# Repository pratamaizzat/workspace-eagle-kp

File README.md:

Merupakan repository kumpulan file eagle untuk project kp

1. Powes Supply Unit
2. Reangkaian Receiver VLC
3. Rangkaian TIA VLC

Pending : Menambahkan komponen filter HPF pada Rangkaian Sheet 2

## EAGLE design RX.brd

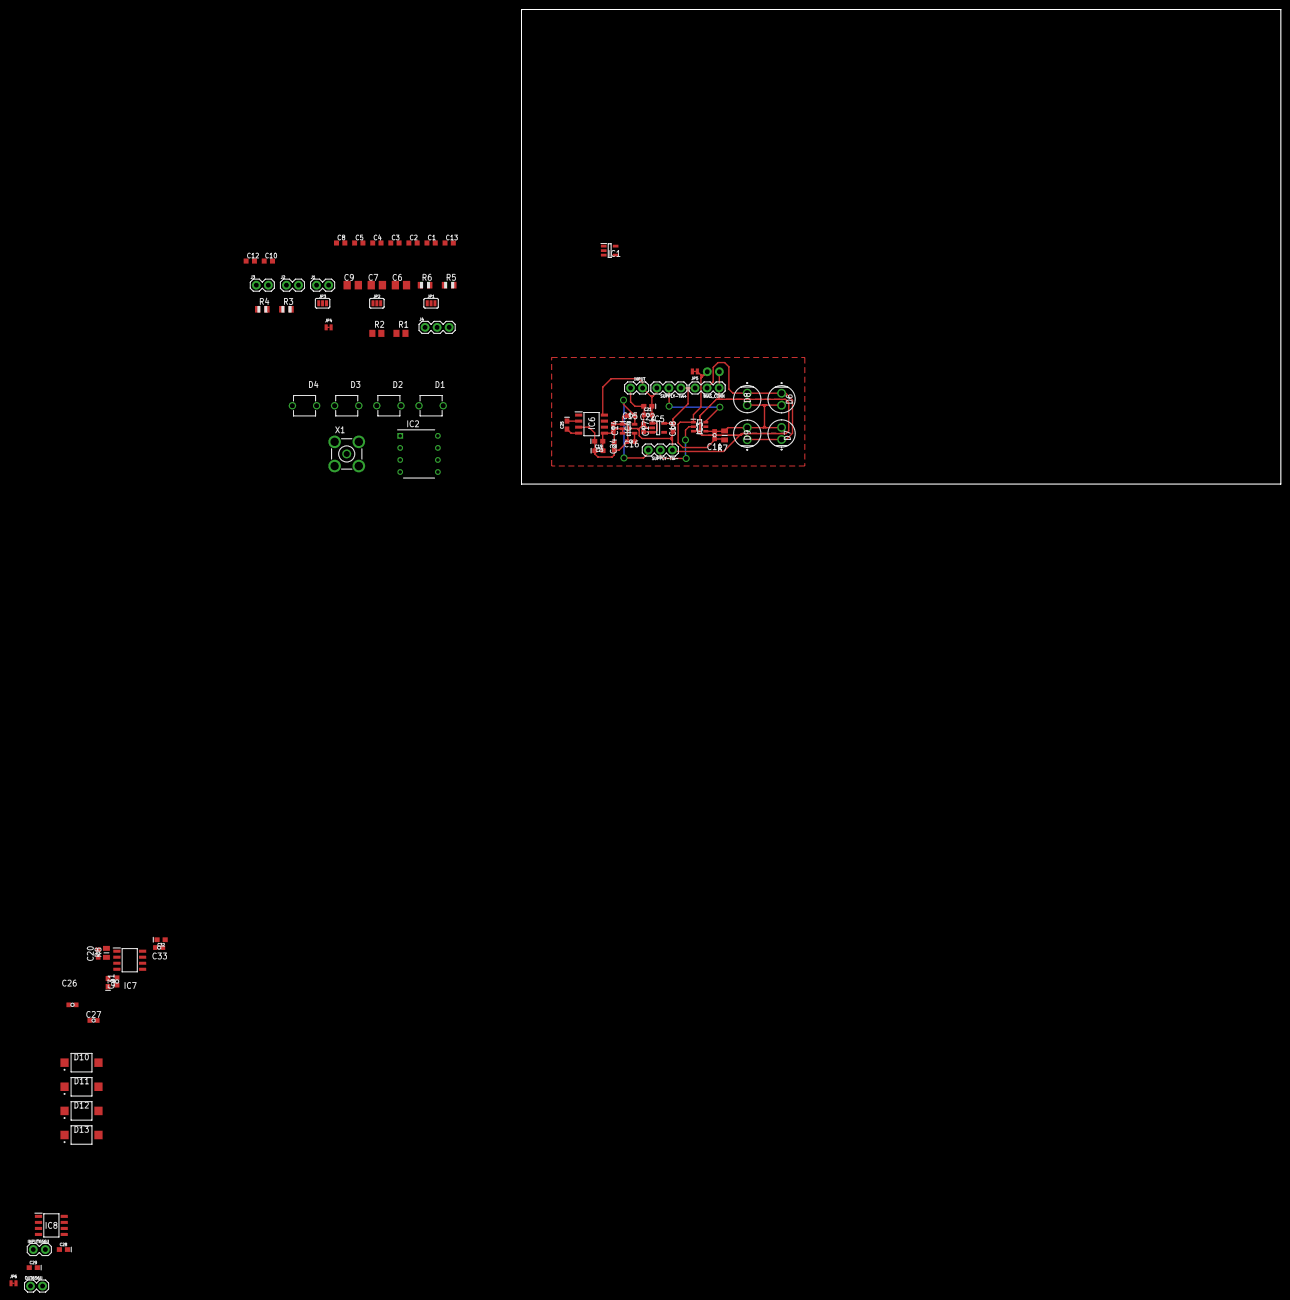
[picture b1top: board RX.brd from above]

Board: 2 copper layers, 160.0 x 100.0 mm, 79 parts (1 on the bottom side), 35 nets.

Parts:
BIAS_CONN: 455-1750-1-ND; 1X03
C1, C2, C3, C4, C5, C8, C10, C12, C13: C0603K
C6, C7, C9: R/2012-12R
C11, C14, C15, C16, C17, C18, C20, C22, C24, C26, C27, C31, C33: 06033C104KAZ2A; CAPC1608X90N
C19, C21, C23, C25, C28, C29, C30, C32: 10uF; 0603-POLAR
D1, D2, D3, D4: BPW34
D6, D7, D8, D9: BPV10NF
D10, D11, D12, D13: VBPW34SR
IC1: OPA354AIDBVR; SOT95P280X145-5N@1
IC2: LM7171BIN_NOPB; DIP794W53P254L959H508Q8N
IC3: LTC6268IS6-10#TRMPBF; SOT95P280X90-6N
IC4: TPS72325DBVTG4; SOT95P280X145-5N
IC5: TLV75525PDBVR; SOT95P280X145-5N
IC6, IC8: TC7662BEOA; SOIC127P600X175-8N
IC7: OPA656U; SOIC127P600X175-8N@1
INPUT, INPUT656U: 1X02
J1, J2, J3: 1X02
J4: 455-1750-1-ND; 1X03
JP1, JP2, JP3: JUMPER-SMT_3_NO_SILK; SMT-JUMPER_3_NO_SILK
JP4, JP5, JP6: JUMPER-SMT_2_NC_TRACE_NO-SILK; SMT-JUMPER_2_NC_TRACE_NO-SILK
OUT656U: 1X02
OUTPUT_LTC: 1X02
R1, R2, R3, R4, R5, R6: R0805
R7, R8: RG2012P-275-B-T5; RESC2012X50N
SUPPLY-TIA+: 455-1750-1-ND; 1X03
SUPPLY-TIA-: 455-1750-1-ND; 1X03
X1: BU-SMA-V

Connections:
5V: C3.2, C4.2, C6.+, C7.+, IC1.5, IC2.7, J4.2
+2.5V: BIAS_CONN.1, C18.2, IC5.5, SUPPLY-TIA+.3
+5V: C17.2, C21.+, C22.2, IC5.1, IC5.3, IC6.8, INPUT.1, SUPPLY-TIA+.1
+V656U: C32.+, C33.2, IC7.7, IC8.8, INPUT656U.1
-2.5V: C15.2, IC4.5, SUPPLY-TIA-.1
-5V: C8.1, C9.-, IC2.4, J4.3
-5V_LTC: C14.2, C19.-, C24.2, IC4.2, IC4.3
-IN: C1.1, C2.2, D1.1, D2.1, D3.1, D4.1, IC1.4, R1.1
-V656U: C29.-, C30.-, C31.2, IC7.4, IC8.5
AMP_IN: JP4.1, R6.1
BIAS_PD: D1.2, D2.2, D3.2, D4.2, JP1.2
GND: C2.1, C3.1, C4.1, C5.1, C6.-, C7.-, C8.2, C9.+, C12.1, J1.2, J2.1, J3.2, J4.1, JP1.3, JP2.3, JP3.3, R2.1, R4.1, X1.2, X1.3, X1.4, X1.5
GND2: BIAS_CONN.3, C14.1, C15.1, C16.1, C17.1, C18.1, C19.+, C21.-, C22.1, C23.+, C24.1, IC3.3, IC4.1, IC5.2, IC6.3, INPUT.2, OUTPUT_LTC.1, SUPPLY-TIA-.3
GND3: C26.1, C27.1, C29.+, C30.+, C31.1, C32.-, C33.1, IC7.3, IC8.3, INPUT656U.2, OUT656U.2
unnamed: IC1.3, JP3.2
unnamed: C20.1, C26.2, C27.2, D10.2, D11.2, D12.2, D13.2, IC7.2, R8.1
unnamed: C1.2, C5.2, IC1.1, J1.1, JP4.2, R1.2, R2.2
unnamed: J3.1, JP1.1
unnamed: IC1.2, JP2.2
unnamed: C10.1, IC2.2, R3.1, R4.2
unnamed: C12.2, IC2.3, R5.2
unnamed: C13.2, R5.1, R6.2
unnamed: C16.2, IC4.4
unnamed: C11.1, IC3.1, JP5.1, OUTPUT_LTC.2, R7.1
unnamed: C25.+, IC6.2
unnamed: C25.-, IC6.4
unnamed: C20.2, IC7.6, JP6.1, OUT656U.1, R8.2
unnamed: C11.2, D6.2, D7.2, D8.2, D9.2, IC3.4, R7.2
unnamed: C28.+, IC8.2
unnamed: C28.-, IC8.4
OUT_AMP: C10.2, C13.1, IC2.6, J2.2, R3.2, X1.1
V+: IC3.6, SUPPLY-TIA+.2
V-: IC3.2, SUPPLY-TIA-.2
V_BIAS: BIAS_CONN.2, D6.1, D7.1, D8.1, D9.1
V_BIAS656U: D10.1, D11.1, D12.1, D13.1

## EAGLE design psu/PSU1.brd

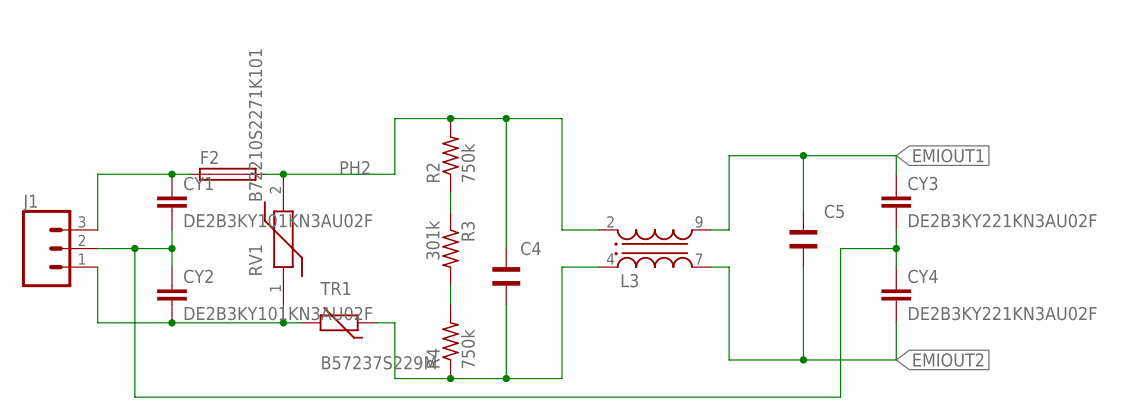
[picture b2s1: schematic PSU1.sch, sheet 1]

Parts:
C4, C5: WCAP-FTXX_890334025039CS; WCAP-FTXX_15X18X14X8
CY1, CY2: DE2B3KY101KN3AU02F; YC7B5
CY3, CY4: DE2B3KY221KN3AU02F; YC7B5
F2: GSH15
J1: CONN_03-SCREW-5MM; SCREWTERMINAL-5MM-3
L3: WE-CMB_L_744824310; WE-CMB_L
R2, R4: 750k; R1206
R3: 301k; R1206
RV1: B72210S2271K101
TR1: B57237S229M; R-7,5

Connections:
EMIOUT1: C5.2, CY3.1, L3.9 (3); also elsewhere on the board
EMIOUT2: C5.1, CY4.2, L3.7 (2); also elsewhere on the board
unnamed: R2.1, R3.1
unnamed: R3.2, R4.2
unnamed: CY1.1, F2.1, J1.3
unnamed: CY2.2, J1.1, RV1.1, TR1.2
unnamed: C4.2, L3.4 (1), R4.1, TR1.1
unnamed: CY1.2, CY2.1, CY3.2, CY4.1, J1.2
PH2: C4.1, F2.2, L3.2 (4), R2.2, RV1.2

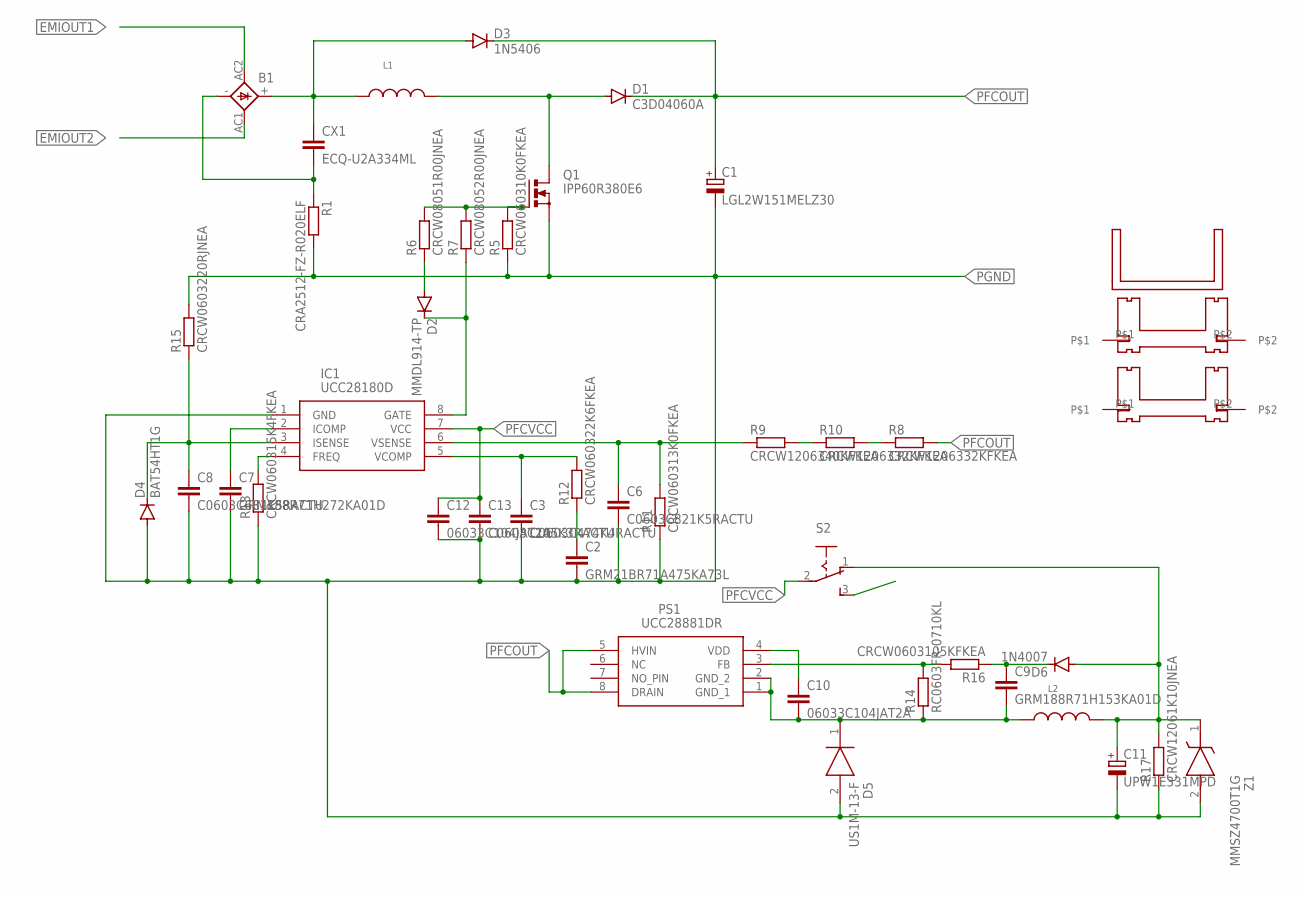
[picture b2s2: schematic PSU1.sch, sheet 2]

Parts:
B1: GBU4S
C1: LGL2W151MELZ30; EB22,5D
C2: GRM21BR71A475KA73L; C0805
C3: C0603C474K4RACTU; C0603
C6: C0603C821K5RACTU; C0603
C7: GRM188R71H272KA01D; C0603
C8: C0603C681K5RACTU; C0603
C9: GRM188R71H153KA01D; C0603
C10, C12: 06033C104JAT2A; C0603
C11: UPW1E331MPD; E5-10,5
C13: C0603C105K3RACTU; C0603
CX1: ECQ-U2A334ML; XC15B10
D1: C3D04060A; TO220ACS
D2: MMDL914-TP; SOD323-R
D3: 1N5406; DO201-15
D4: BAT54HT1G; SOD323-R
D5: US1M-13-F; SODFL5226X240N
D6: 1N4007; DO41-7.6
IC1: UCC28180D; SOIC127P600X175-8N
L1: WE-HCF_ROUND_74437529203471; WE-HCF_ROUND
L2: WE-TIS_1111_7447471102; WE-TIS_1111
PS1: UCC28881DR; SOIC127P600X175-8N
Q1: IPP60R380E6; TO220BV
R1: CRA2512-FZ-R020ELF; R2512W
R5: CRCW060310K0FKEA; R0603
R6: CRCW08051R00JNEA; R0805
R7: CRCW08052R00JNEA; R0805
R8, R10: CRCW1206332KFKEA; R1206
R9: CRCW1206340KFKEA; R1206
R11: CRCW060313K0FKEA; R0603
R12: CRCW060322K6FKEA; R0603
R13: CRCW060315K4FKEA; R0603
R14: RC0603FR-0710KL; R0805
R15: CRCW0603220RJNEA; R0603
R16: CRCW0603105KFKEA; R0805
R17: CRCW12061K10JNEA; R1206
S2: 255SB
U$1, U$3: HEAT001; HEAT01
U$2: HEAT002; HEAT02
Z1: MMSZ4700T1G; SOD3716X135N

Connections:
DMOS1: D1.A, L1.2, Q1.D
EMIOUT1: B1.AC2 (AC1); also elsewhere on the board
EMIOUT2: B1.AC1 (AC2); also elsewhere on the board
unnamed: Q1.G, R5.2, R6.2, R7.2
unnamed: B1.-, CX1.2, R1.1
unnamed: B1.+, CX1.1, D3.A, L1.1
unnamed: D2.A, R6.1
unnamed: D2.C, IC1.8 (GATE), R7.1
unnamed: R8.1, R10.2
unnamed: R9.2, R10.1
unnamed: C6.1, IC1.6 (VSENSE), R9.1, R11.2
unnamed: C3.1, IC1.5 (VCOMP), R12.2
unnamed: IC1.4 (FREQ), R13.2
unnamed: C8.1, D4.C, IC1.3 (ISENSE), R15.1
unnamed: C7.1, IC1.2 (ICOMP)
unnamed: C2.1, R12.1
unnamed: C9.2, C10.2, D5.1 (K), L2.1, PS1.1 (GND_1), PS1.2 (GND_2), R14.1
unnamed: PS1.3 (FB), R14.2, R16.2
unnamed: C9.1, D6.C, R16.1
unnamed: C11.+, D6.A, L2.2, R17.2, S2.1 (O), Z1.1 (K)
unnamed: C10.1, PS1.4 (VDD)
PFCOUT: C1.+, D1.C, D3.C, PS1.5 (HVIN), PS1.8 (DRAIN), R8.2
PFCVCC: C12.1, C13.1, IC1.7 (VCC), S2.2
PGND: C1.-, C2.2, C3.2, C6.2, C7.2, C8.2, C11.-, C12.2, C13.2, D4.A, D5.2 (A), IC1.1 (GND), Q1.S, R1.2, R5.1, R11.1, R13.1, R15.2, R17.1, Z1.2 (A)

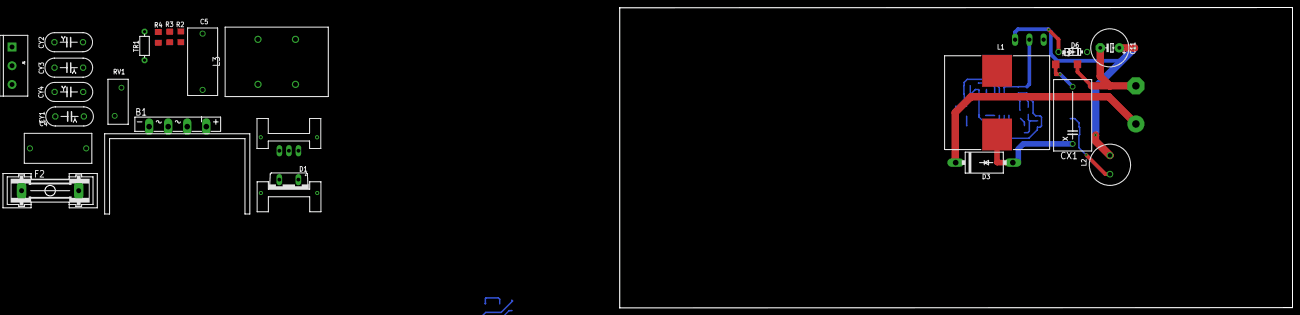
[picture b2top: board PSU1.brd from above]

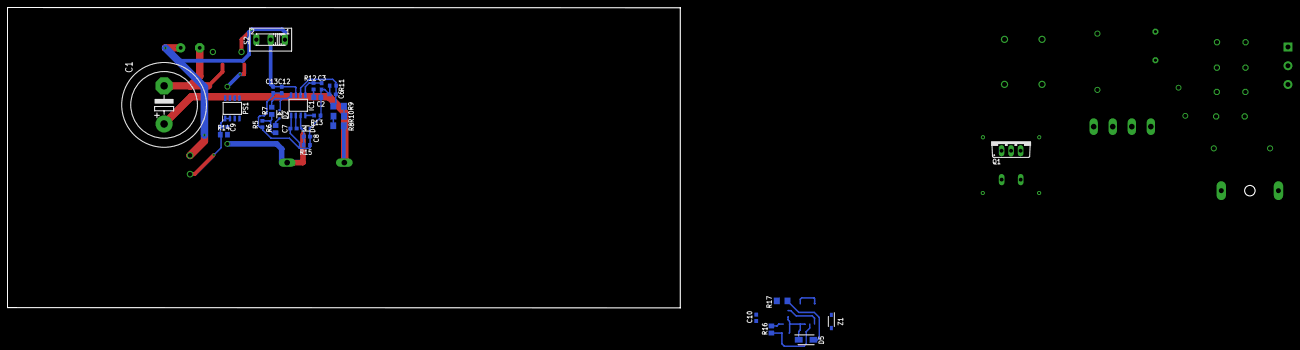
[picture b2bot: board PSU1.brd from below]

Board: 2 copper layers, 179.3 x 80.1 mm, 57 parts (31 on the bottom side), 31 nets.

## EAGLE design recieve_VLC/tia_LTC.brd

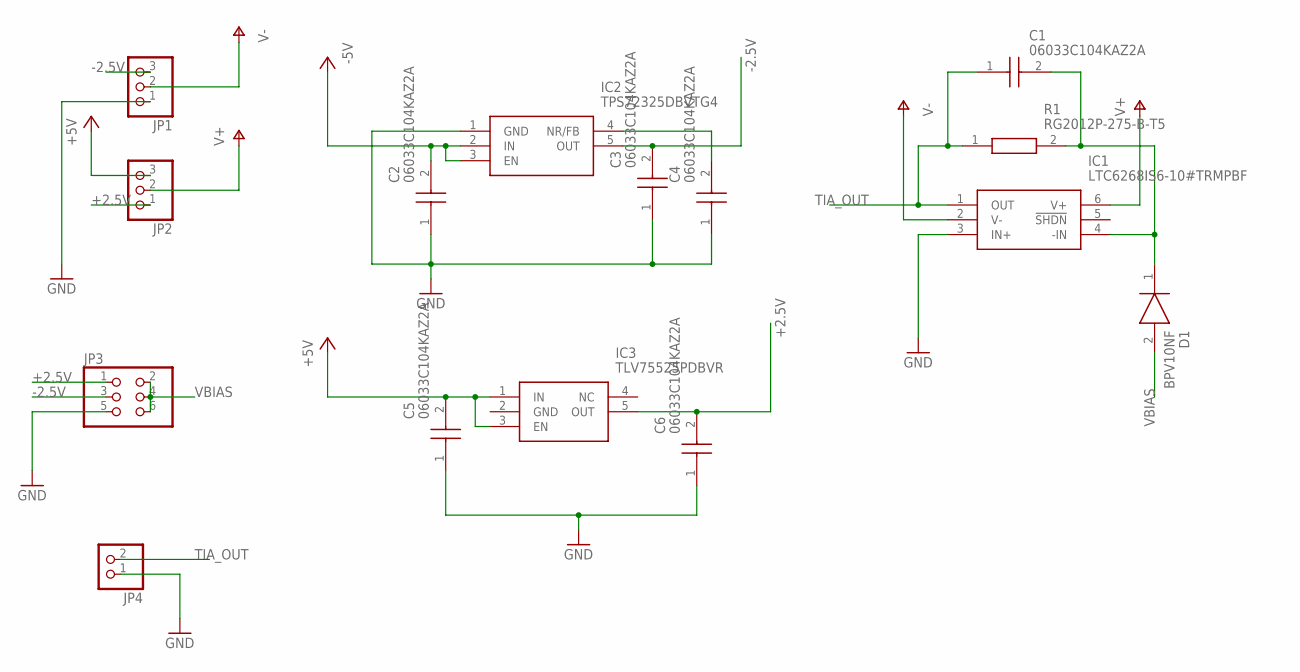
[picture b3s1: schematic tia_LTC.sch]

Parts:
C1, C2, C3, C4, C5, C6: 06033C104KAZ2A; CAPC1608X90N
D1: BPV10NF
IC1: LTC6268IS6-10#TRMPBF; SOT95P280X90-6N
IC2: TPS72325DBVTG4; SOT95P280X145-5N
IC3: TLV75525PDBVR; SOT95P280X145-5N
JP1, JP2: PINHD-1X3; 1X03
JP3: PINHD-2X3; 2X03
JP4: PINHD-1X2; 1X02
R1: RG2012P-275-B-T5; RESC2012X50N

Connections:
+2.5V: C6.2, IC3.5 (OUT), JP2.1, JP3.1
+5V: C5.2, IC3.1 (IN), IC3.3 (EN), JP2.3
-2.5V: C3.2, IC2.5 (OUT), JP1.3, JP3.3
-5V: C2.2, IC2.2 (IN), IC2.3 (EN)
GND: C2.1, C3.1, C4.1, C5.1, C6.1, IC1.3 (IN+), IC2.1 (GND), IC3.2 (GND), JP1.1, JP3.5, JP4.1
unnamed: C1.2, D1.1 (K), IC1.4 (-IN), R1.2
unnamed: C4.2, IC2.4 (NR/FB)
TIA_OUT: C1.1, IC1.1 (OUT), JP4.2, R1.1
V+: IC1.6 (V+), JP2.2
V-: IC1.2 (V-), JP1.2
VBIAS: D1.2 (A), JP3.2, JP3.4, JP3.6

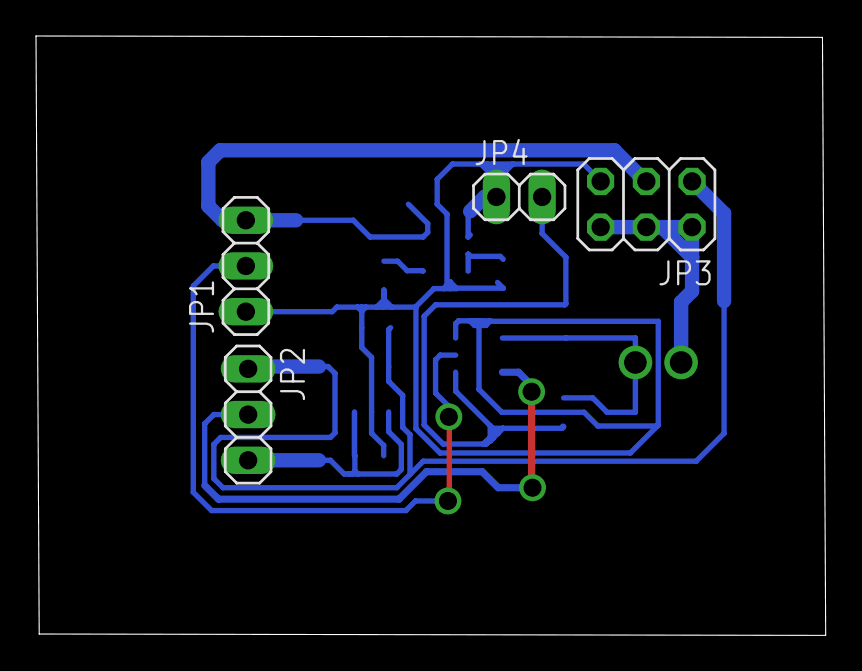
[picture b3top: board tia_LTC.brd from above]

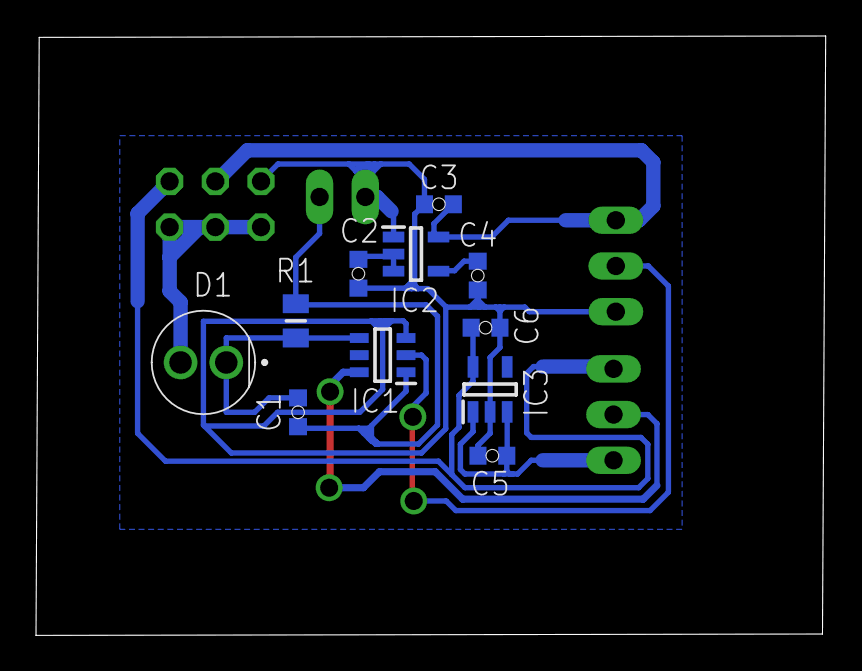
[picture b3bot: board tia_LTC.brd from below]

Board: 2 copper layers, 43.9 x 33.3 mm, 15 parts (11 on the bottom side), 11 nets.

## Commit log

2020-03-16 Initial README.md
2020-03-17 memberikan komponen kompnen yang dibutukan pada rangkaian TIA dengan IC LTC6268 kecuali filter untuk HPF
2020-03-17 menambahkan pending project pada README.md
2020-03-17 Menambahakan komponen komponen yang diperlukan untuk OPA656U kurang HPF untuk rangkaian OPA656U
2020-03-17 melakukan routing untuk sheet 2 , belum ada filter

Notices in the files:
parts and their libraries:
SparkFun-Connectors: Licensing: Creative Commons ShareAlike 4.0 International - https://creativecommons.org/licenses/by-sa/4.0
Wurth_Elektronik_Passive_Capacitors_rev1: Copyright: Würth Elektronik
